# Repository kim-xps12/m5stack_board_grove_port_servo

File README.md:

## About
M5StackシリーズのGroveコネクタからサーボモータを直接駆動する際に便利な基板です．一部のｽﾀｯｸﾁｬﾝキットで使用されています．
This is borad for connecing a servo mortor from M5Stack series Grove connector. Some kit of stack-chan include this.

## BOM
|  Item  |  Model number  |  Link  |
| ---- | ---- | ---- |
|  Connector  |  B4B-PH-K-S  | [akitsuki](https://akizukidenshi.com/catalog/g/gC-12804/)  |
|  Connector  |  Pin header (2x3, 2.54mm)  | [akitsuki](https://akizukidenshi.com/catalog/g/gC-16883/)  |
|  Capacitor  |  Electrolytic, 35V, 100uF  | [akitsuki](https://akizukidenshi.com/catalog/g/gP-02724/)  |

## Assembly

## Environment
- Windows 11
- KiCAD 7.0

## LICENCE
MITライセンスでの公開です．頒布などの使い方をされる場合はご一報いただけると個人的に喜びます．
It is released under the MIT license. I would appreciate it if you could let us know if you plan on distributing it or using it.
(Twitter: eternalfriend17)

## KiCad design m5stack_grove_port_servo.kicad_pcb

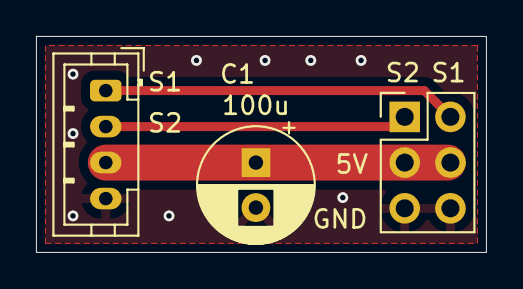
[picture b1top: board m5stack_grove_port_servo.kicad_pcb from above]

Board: 2 copper layers, 25.0 x 12.0 mm, 3 parts (0 on the bottom side), 4 nets.

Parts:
C1: 100u; CP_Radial_D6.3mm_P2.50mm
J1: B4B-PH-K-S(LF)(SN); JST_PH_B4B-PH-K_1x04_P2.00mm_Vertical
J2: Conn_02x03_Odd_Even; PinHeader_2x03_P2.54mm_Vertical

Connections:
+5V: C1.1, J1.3, J2.3, J2.4
/PWM1: J1.1, J2.2
/PWM2: J1.2, J2.1
GND: C1.2, J1.4, J2.5, J2.6

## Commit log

2023-10-16 first commit for publish
2023-10-16 update readme, environment
2023-10-16 Create LICENSE
2023-10-16 Update README.md, add picture
